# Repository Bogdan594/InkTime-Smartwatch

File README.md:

# InkTime - SmartWatch Project
InkTime este un concept de ceas inteligent axat pe eficienta energetica, utilizand un display e-Paper.

## Diagrama Bloc
```
┌─────────────────────────────────────────────────────────────┐
│                   SUBSISTEM ALIMENTARE                      │
│                                                             │
│  Port USB-C ─────► USBLC6-2SC6 (Protecție ESD)              │
│                          │                                  │
│                          ▼                                  │
│  Baterie Li-Po ◄────► BQ25180 (Încărcător IC)               │
│  (Test Pads)             │                                  │
│                          ▼                                  │
│                   RT6160AWSC (Buck-Boost) ──► VCC (3.3V)    │
│                          │                      (Sistem)    │
│                          ▼                                  │
│  MAX17048 (Fuel Gauge) ──► Monitorizare prin I2C            │
└─────────────────────────────────────────────────────────────┘

┌─────────────────────────────────────────────────────────────┐
│                  UNITATE DE PROCESARE                       │
│                                                             │
│              nRF52840 (MCU + Bluetooth LE)                  │
│        ┌─────────────┬─────────────┬─────────────┐          │
│        │             │             │             │          │
│     Bus SPI       Bus I2C       GPIOs        Antenă RF      │
│        │             │             │             │          │
│        ▼             │             ▼             ▼          │
│  Display e-Paper     │       3x Butoane      Johanson       │
│   (J1 - 24 pin)      │      (UP, DN, ENT)    2.45GHz        │
│                      │                                      │
│        ┌─────────────┴─────────────┐                        │
│        │                           │                        │
│        ▼                           ▼                        │
│  BMA423 (Accel.)          DRV2605L (Haptic)                 │
│  (Senzor mișcare)         (Motor Vibrații)                  │
└─────────────────────────────────────────────────────────────┘
```

## Bill of Materials

| Qty | Value | Device | Package | Parts | Description |
| :--- | :--- | :--- | :--- | :--- | :--- |
| 1 | - | ESP32_C6_LIBRARY_JUMPER | JUMPER_SJ | SJ1 | SMD solder JUMPER |
| 3 | 0 | CPF0201D7K68C1 | 0201 | R2, R3, R4 | 7.68k 0201 Thin Film Resistor |
| 4 | 0.1uF | GRM011R60J152KE01L | CAPC0201 | C23, C27, C34, C42 | SMD Capacitor X5R 6.3V |
| 1 | 0.1uF/50V | NRF_3_CAPACITOR_0201 | RESC0201 | EPD_C5 | Generic chip capacitor |
| 7 | 0.1uF/50V | NRF_3_CAPACITOR_0402 | RESC0402 | EPD_C6, EPD_C7, EPD_C8, EPD_C9, EPD_C10, EPD_C11, EPD_C12 | Generic chip capacitor |
| 1 | 0.47 | CPF0201D7K68C1 | 0201 | R1_EP_DR | 7.68k 0201 Resistor |
| 1 | 1.0uF | PERFECT_0402_CAP | 0402 | C15 | 0402 (1005 Metric) |
| 5 | 100nF | NRF_3_CAPACITOR_0201 | RESC0201 | C5, C7, C8, C12, C19 | Generic chip capacitor |
| 1 | 100pF | NRF_3_CAPACITOR_0201 | RESC0201 | C11 | Generic chip capacitor |
| 3 | 10K | CPF0201D7K68C1 | 0201 | R2_EP_DR, R9, R_PWR_EPD | 7.68k 0201 Resistor |
| 3 | 10k | CPF0201D7K68C1 | 0201 | R5, R7, R8 | 7.68k 0201 Resistor |
| 1 | 10uF | NRF_3_CAPACITOR_0402 | RESC0402 | C1-EP-DR | Generic chip capacitor |
| 2 | 10uF | PERFECT_0402_CAP | 0402 | C24, C39 | 0402 (1005 Metric) |
| 1 | 10uH | NRF_2_INDUCTOR_0402 | RESC0402 | L2 | Generic chip inductor |
| 4 | 12pF | NRF_3_CAPACITOR_0201 | RESC0201 | C1, C2, C17, C18 | Generic chip capacitor |
| 1 | 15nH | NRF_2_INDUCTOR_0402 | RESC0402 | L3 | Generic chip inductor |
| 2 | 1pF | NRF_3_CAPACITOR_0201 | RESC0201 | C3, C4 | Generic chip capacitor |
| 6 | 1uF | GRM011R60J152KE01L | CAPC0201 | C29, C30, C31, C32, C37, C38 | SMD Capacitor X5R 6.3V |
| 2 | 1uF/50V | NRF_3_CAPACITOR_0402 | RESC0402 | EPD_C1, EPD_C2 | Generic chip capacitor |
| 1 | 2.2 | CPF0201D7K68C1 | 0201 | R_TYPE_SEL | 7.68k 0201 Resistor |
| 3 | - | EVP-AKE31ASW | SW_EVP-AKE31A | SW_DN, SW_ENT, SW_UP | Panasonic Tactile Switch |
| 1 | 20V/4.2A | MOSFET_PCH-DMG2305UX | SOT23-3 | Q1 | P-channel MOSFET |
| 2 | 22uF | PERFECT_0402_CAP | 0402 | C25, C33 | 0402 (1005 Metric) |
| 1 | 2450AT18B100E | 2450AT18B100E | ANTC3216 | ANT1 | Antennas 2.45GHz ANTENNA |
| 1 | 3.9nH | NRF_2_INDUCTOR_0402 | RESC0402 | L1 | Generic chip inductor |
| 1 | 32.768kHz | NRF_1_XTAL_32KHZ | XTAL_3215 | X2 | Crystal Oscillator |
| 1 | 32MHz | NRF_XTAL_32MHZ | BT-XTAL_2016 | X1 | Crystal Oscillator |
| 2 | 3K3 | CPF0201D7K68C1 | 0201 | R17, R18 | 7.68k 0201 Resistor |
| 2 | 4.7uF | NRF_3_CAPACITOR_0402 | RESC0402 | C14, C43 | Generic chip capacitor |
| 1 | 4.7uF/25V | NRF_3_CAPACITOR_0402 | RESC0402 | C2-EP-DR | Generic chip capacitor |
| 3 | 4.7µF | PERFECT_0402_CAP | 0402 | C6, C20, C21 | 0402 (1005 Metric) |
| 1 | 47nF | PERFECT_0402_CAP | 0402 | C16 | 0402 (1005 Metric) |
| 1 | 503480-2400 | 503480-2400 | 5034802400 | J1 | 0.5mm FPC RA SMT 24Ckt |
| 2 | 5K1 | CPF0201D7K68C1 | 0201 | R1_USB, R2_USB | 7.68k 0201 Resistor |
| 1 | 68uH | 744043680IND | IND_4828 | L5 | Wurth Electronics Inductor |
| 1 | 820pF | NRF_3_CAPACITOR_0201 | RESC0201 | C9 | Generic chip capacitor |
| 1 | BMA421 | BMA423 | BMA423 | IC3 | Accelerometer Triaxial |
| 1 | BQ25180YBGR | BQ25180YBGR | BGA8 | IC1 | Charger IC Li-Ion/Polymer |
| 1 | DRV2605YZFR | DRV2605YZFR | BGA9 | IC2 | Haptic Driver |
| 1 | FTC252012S | MLP2016SR47 | INDC2016 | L7 | SMD / SMT Inductor 0.47uH |
| 14 | - | HECTOR_WATCH_TP | TP20R | TP_3.3V ... TP_VREG | Test pads |
| 1 | KH-TYPE-C-16P | KH-TYPE-C-16P | SMT | J4 | USB Type-C Connector |
| 1 | MAX17048G+T | MAX17048G | SON50P200 | U3 | Fuel Gauge with ModelGauge |
| 3 | MBR0530 | MBR0530 | SOD3716 | D2, D4, D5 | Schottky Diode 0.5A 30V |
| 3 | N.C. | NRF_3_CAPACITOR_0201 | RESC0201 | C10, C13, C22 | Not Connected |
| 1 | NRF52840_QF | NRF52840_QF | AQFN-74 | U1 | nRF52840 SoC |
| 1 | RT6160AWSC | RT6160AWSC | BGA15 | IC9 | Buck-Boost Regulator |
| 1 | SI1308EDL | SI1308EDL | SOT65P210

## Functionalitati Hardware

- Unitate Centrala: nRF52840 gestioneaza logica sistemului si conexiunea Bluetooth 5.4 prin arhitectura ARM Cortex-M4F.
- Afisaj: Ecranul e-Paper de 1.54" utilizeaza interfata SPI pentru a mentine imaginea afisata cu consum zero de energie.
- Senzori Miscare: Accelerometrul BMA423 comunica prin I2C pentru a detecta pasii si gesturile de activare a ecranului.
- Feedback Haptic: Driverul DRV2605L utilizeaza magistrala I2C pentru a genera efecte de vibratie precise prin motorul intern.
- Gestiune Energie: Integratul BQ25180 controleaza incarcarea bateriei prin USB-C, asigurand protectia si longevitatea celulei Li-Po.
- Stabilizare Tensiune: Regulatorul Buck-Boost RT6160A mentine un prag constant de 3.3V necesar functionarii stabile a componentelor.
- Monitorizare Baterie: Cipul MAX17048 raporteaza prin I2C nivelul de incarcare (SOC%) folosind algoritmi de masurare fara rezistor de sunt.
- Eficienta: Combinatia dintre MCU-ul ultra-low-power si display-ul e-Paper permite o autonomie estimata de peste 60 de zile.

## Configuratia pinilor nRF52840

- Bus SPI (P0.11-P0.15): Folosit pentru Display-ul e-Paper deoarece asigura latimea de banda mare necesara pentru transferul rapid al bufferului de imagine.
- Bus I2C (P0.26, P0.27): Conecteaza senzorii (BMA423, MAX17048) si driverele (DRV2605, BQ25180) pe aceleasi doua fire pentru a minimiza numarul de trasee pe PCB.
- Pini Butoane (P0.02, P0.03, P0.28): Alocati ca intrari digitale cu intreruperi (GPIOTE) pentru a permite trezirea instanta a ceasului din modul de consum redus (Deep Sleep).
- Pin Busy Display (P0.16): Intrare digitala care permite MCU-ului sa astepte pana cand ecranul termina procesul fizic de refresh inainte de a trimite noi date.
- Pin Interrupt BMA423 (P0.19): Conectat la MCU pentru a semnaliza detectia miscarii (wrist-tilt) fara ca procesorul sa interogheze constant senzorul, economisind energie.
- Pin Enable Haptic (P0.20): Pin de control rapid pentru driverul DRV2605L, utilizat pentru a declansa secventele de vibratii sincronizate cu notificarile.
- Pini Cristal 32MHz (XC1, XC2): Pini dedicati pentru oscilatorul extern de mare precizie, critic pentru functionarea corecta a radioului Bluetooth Low Energy.
- Pini Cristal 32.768kHz (P0.00, P0.01): Folositi pentru ceasul de timp real (RTC) care asigura masurarea precisa a orei cu un consum de curent de ordinul microamperilor.
- Pini SWD (SWDIO, SWDCLK): Interfata dedicata de programare si debug, absolut necesara pentru incarcarea firmware-ului si monitorizarea variabilelor in timp real.
- Pin Reset (P0.18): Configurat ca intrare de reset hardware pentru a permite repornirea sigura a sistemului in cazul unui blocaj software (Watchdog/Manual).

## Decizii luate
- Am acceptat erorile de overlap pe pinii procesorului cauzate de via-uri deoarece nu am gasit o alta metoda de a trage cablu pana acolo.
- Am acceptat erorile de copper clearence pentru ca orice alta solutie ar fi ingreunat si mai tare asezarea cablurilor.
- Am acceptat erorile de airwire intrucat gasirea unui traseu intre 2 acei pini ar fi provocat mai multe erori de alte tipuri

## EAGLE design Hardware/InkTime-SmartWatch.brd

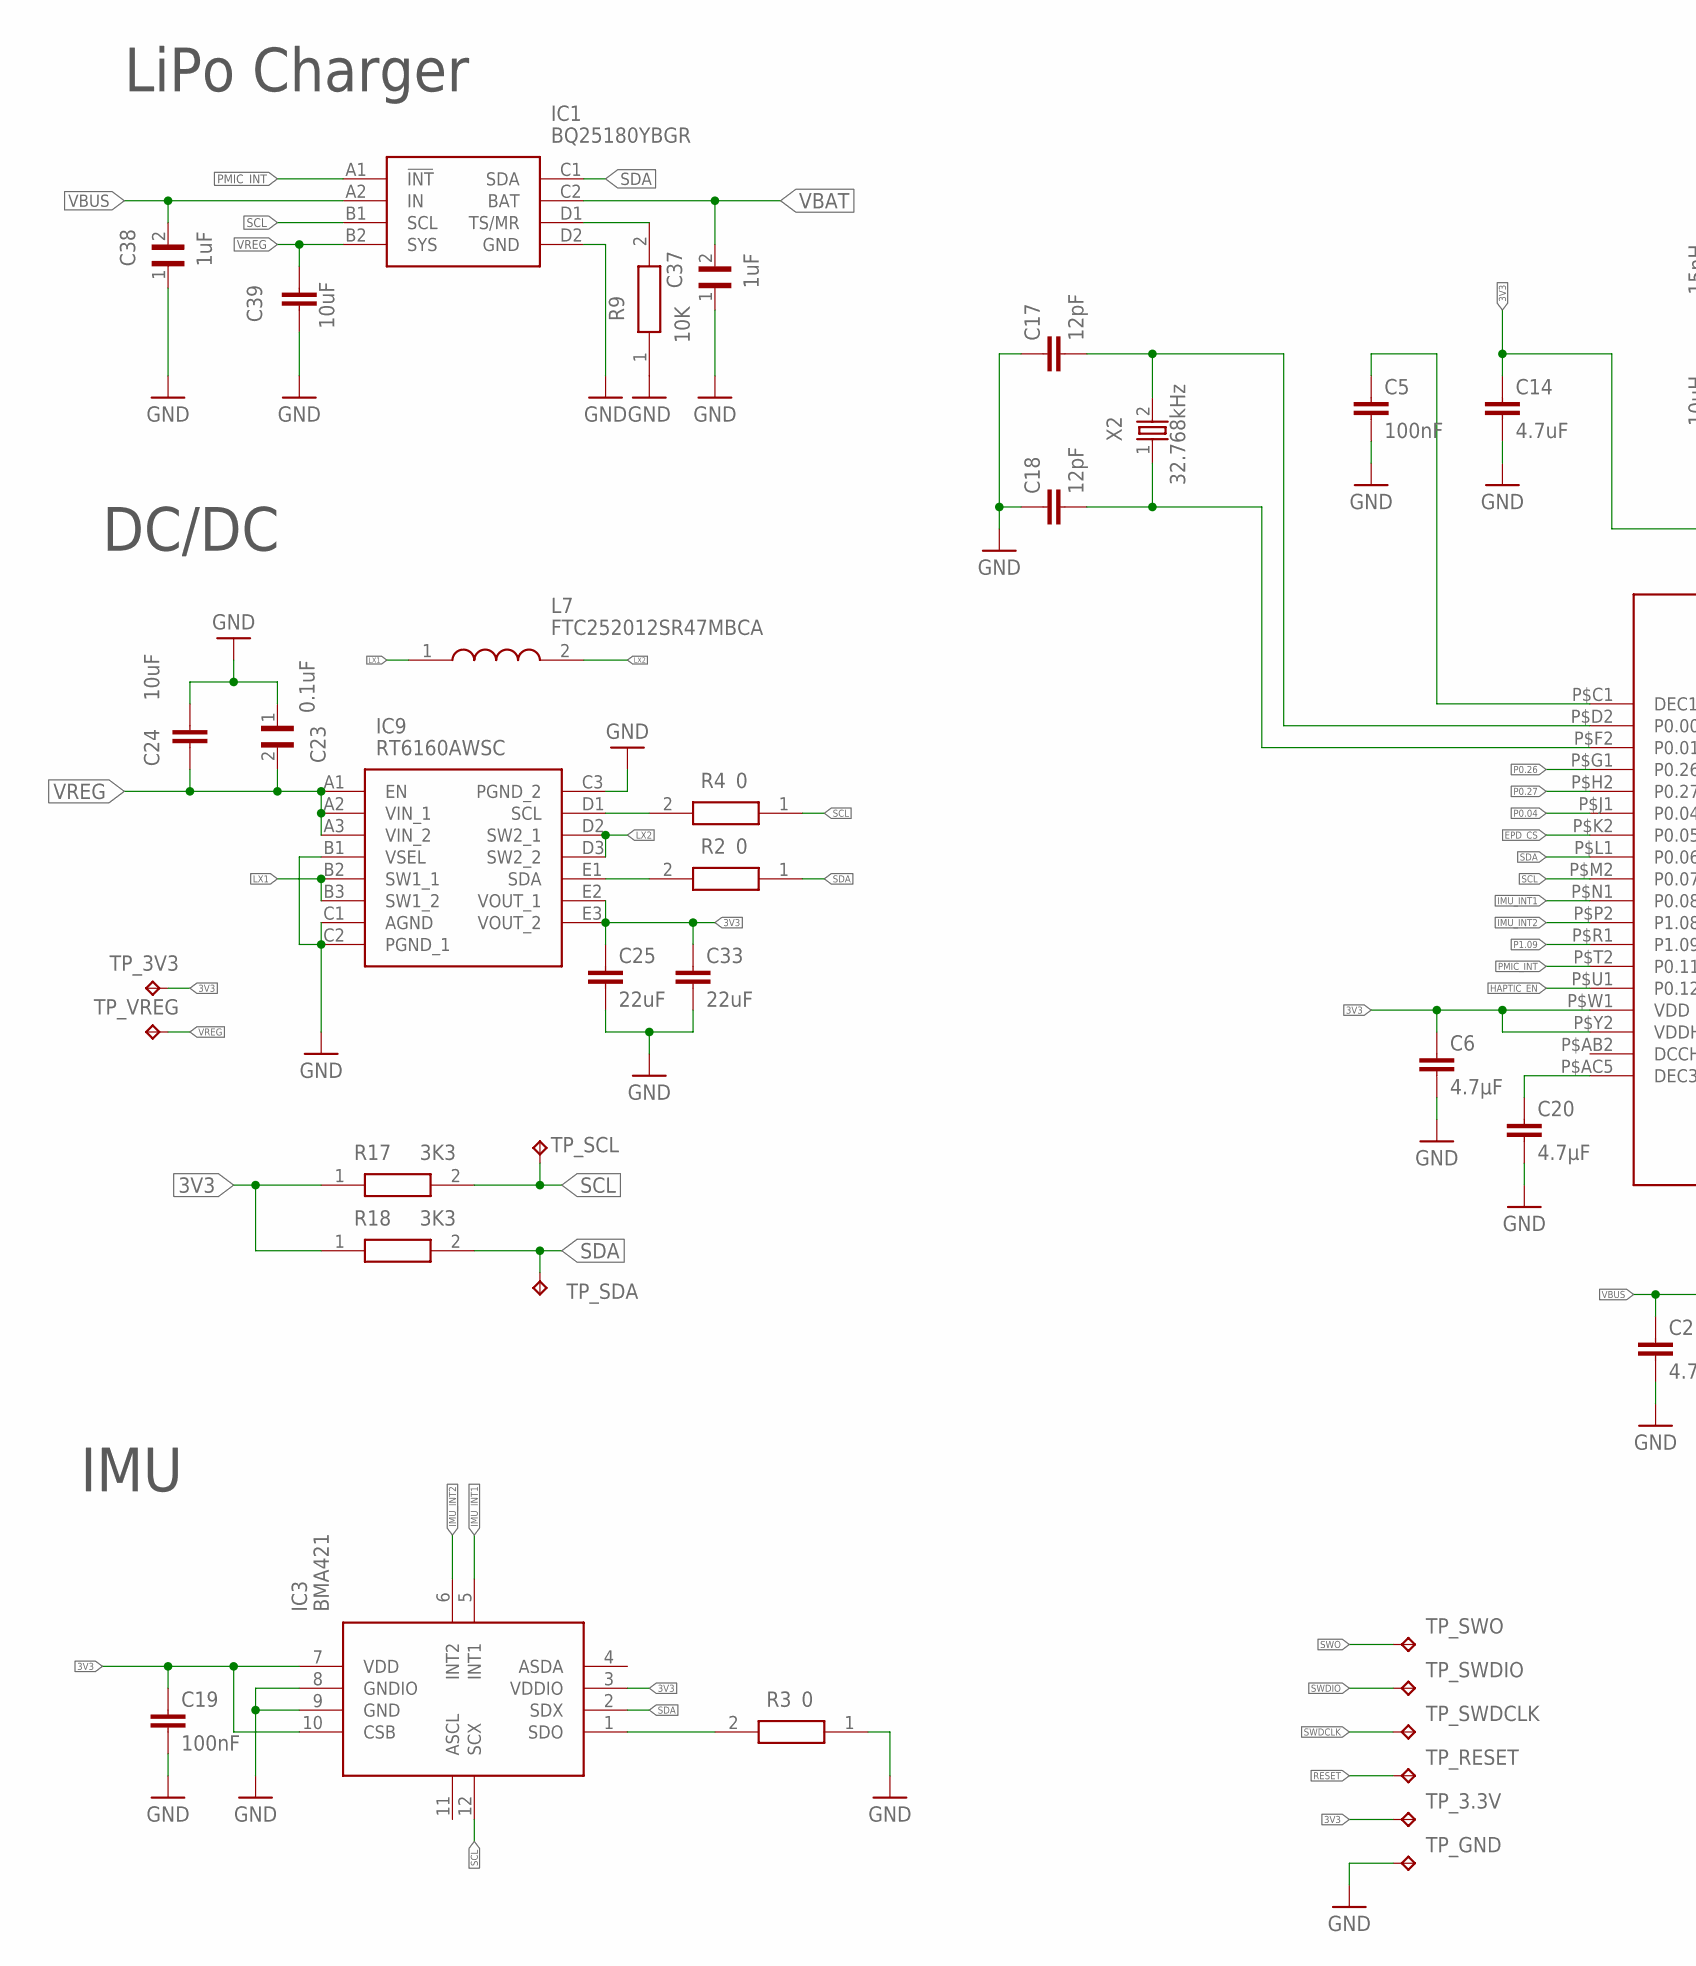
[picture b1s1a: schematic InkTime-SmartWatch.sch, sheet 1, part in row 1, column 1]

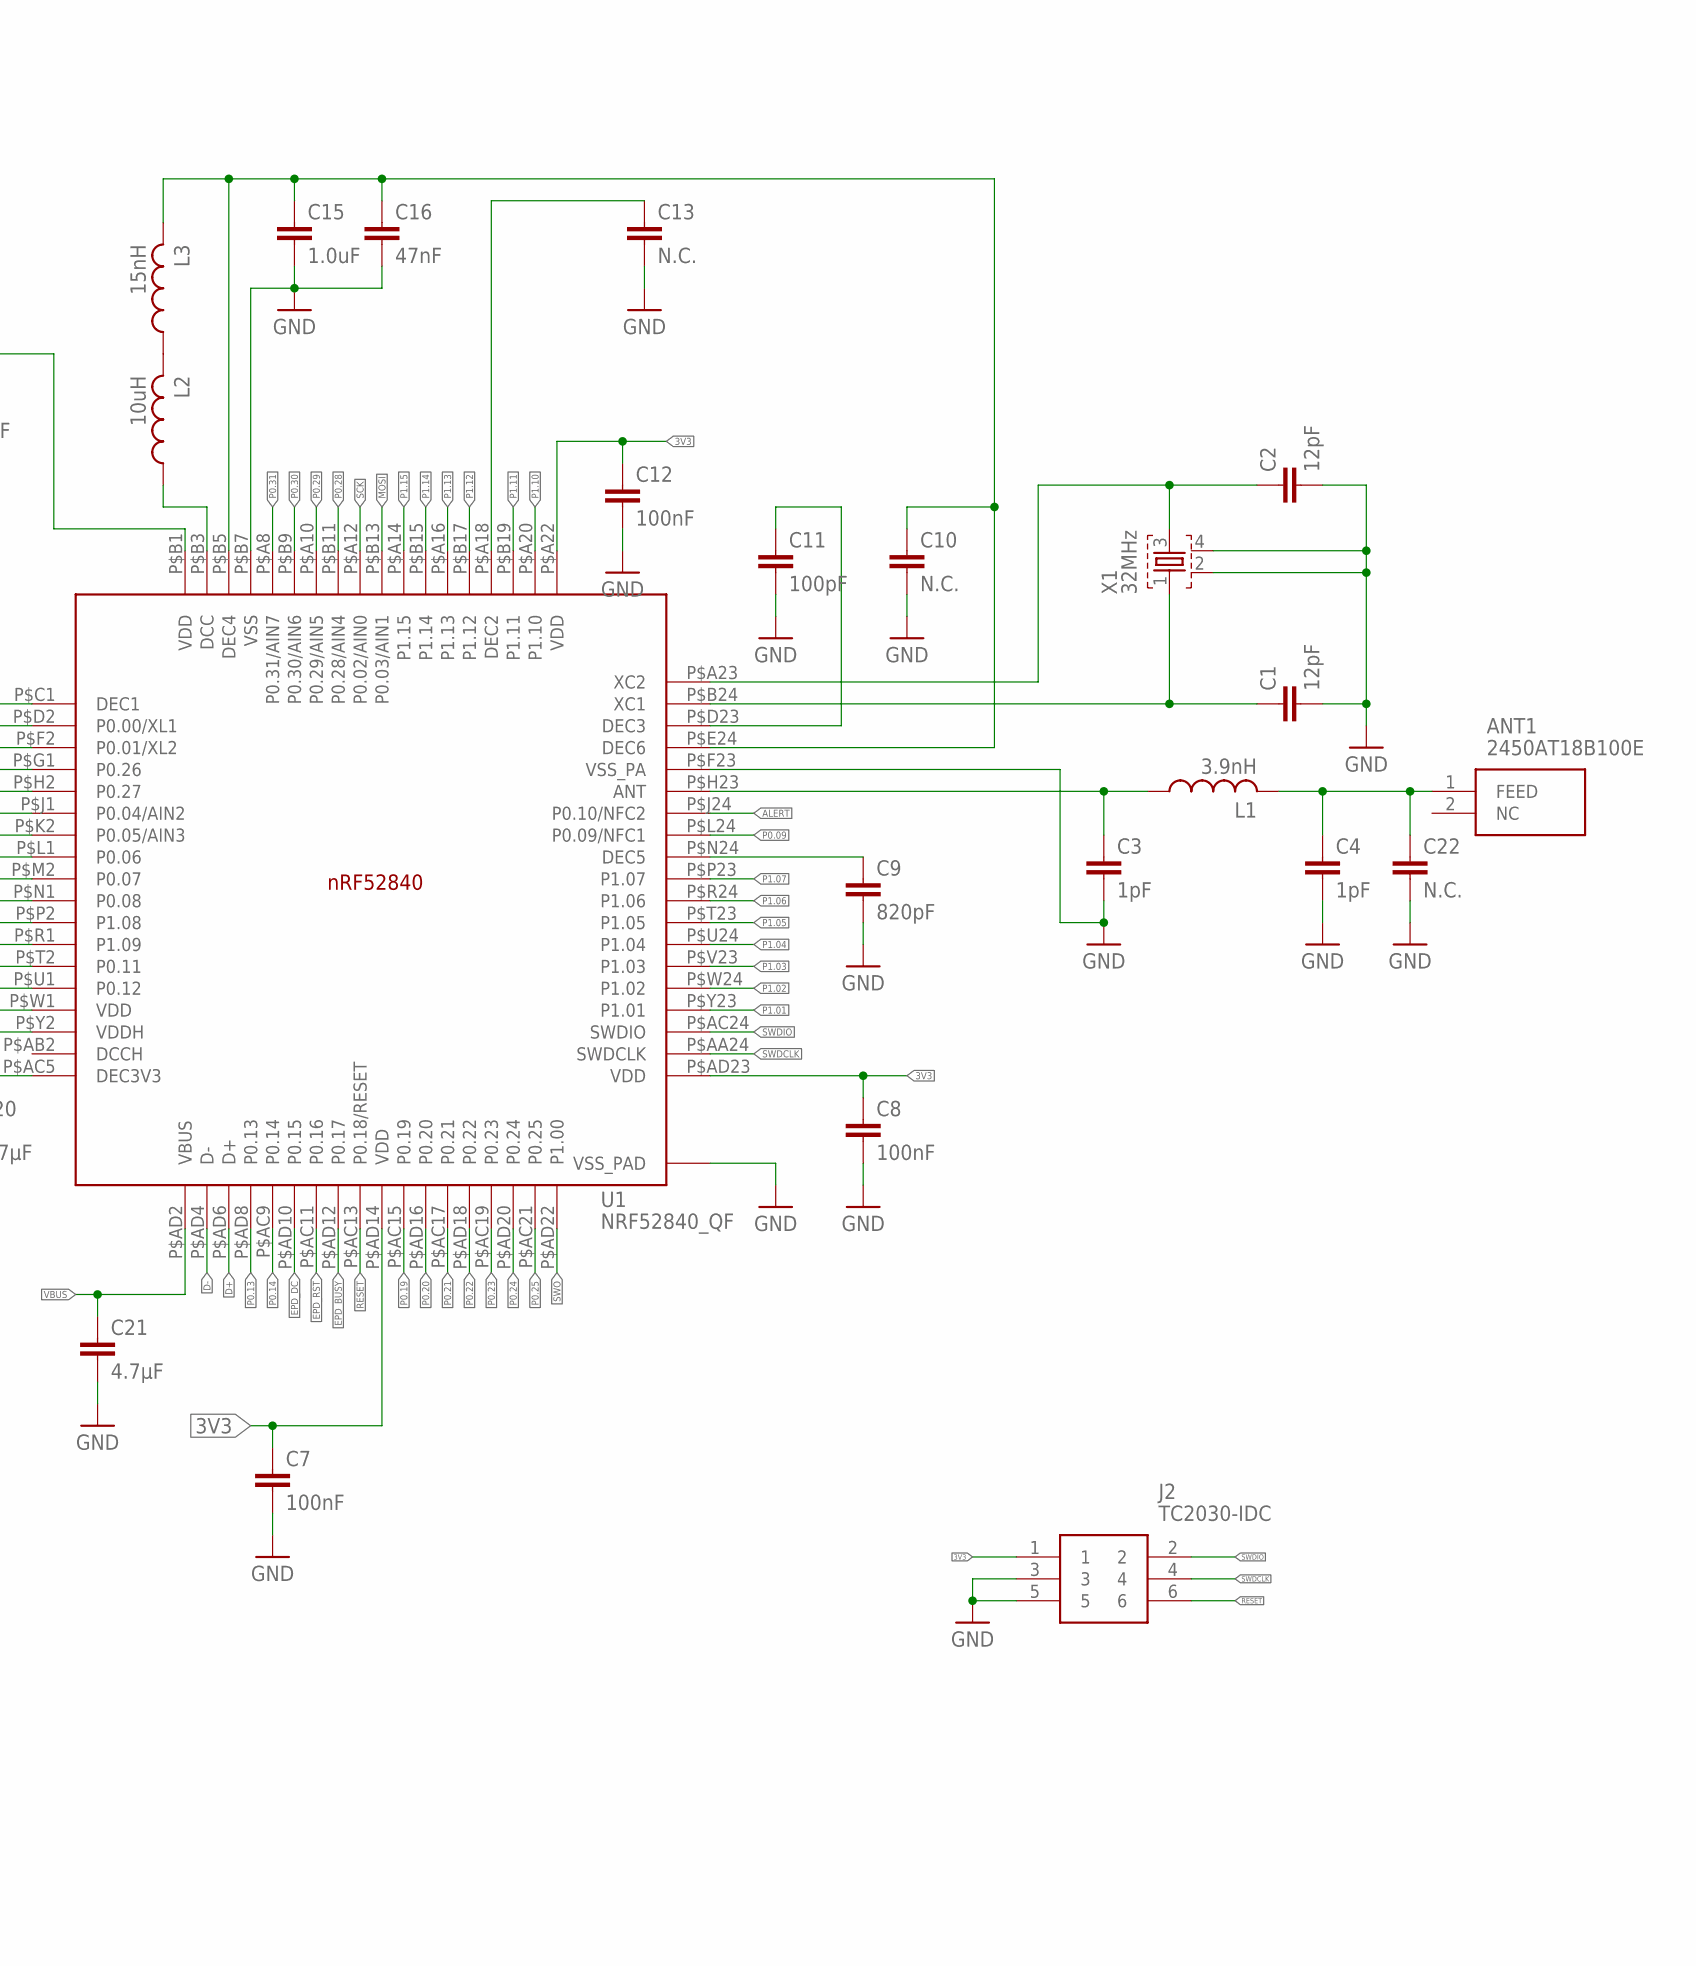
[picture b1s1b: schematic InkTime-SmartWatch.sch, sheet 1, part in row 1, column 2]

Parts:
ANT1: 2450AT18B100E; 2450AT18B100E_ANTC3216X140N
C1, C2, C17, C18: 12pF; NORDIC_NRF_3_RESC0201_L
C3, C4: 1pF; NORDIC_NRF_3_RESC0201_L
C5, C7, C8, C12, C19: 100nF; NORDIC_NRF_3_RESC0201_L
C6, C20, C21: 4.7μF; PERFECT_0402_0402
C9: 820pF; NORDIC_NRF_3_RESC0201_L
C10, C13, C22: N.C.; NORDIC_NRF_3_RESC0201_L
C11: 100pF; NORDIC_NRF_3_RESC0201_L
C14: 4.7uF; NORDIC_NRF_3_RESC0402_L
C15: 1.0uF; PERFECT_0402_0402
C16: 47nF; PERFECT_0402_0402
C23: 0.1uF; GRM011R60J152KE01L_2_CAPC0201X13N
C24, C39: 10uF; PERFECT_0402_0402
C25, C33: 22uF; PERFECT_0402_0402
C37, C38: 1uF; GRM011R60J152KE01L_2_CAPC0201X13N
IC1: BQ25180YBGR; BQ25180YBGR_BGA8C40P2X4_100X155X50
IC3: BMA421; BMA423_BMA423
IC9: RT6160AWSC; RT6160AWSC_BGA15C40P3X5_140X230X60
J2: TC2030-IDC; TC2030-IDC_TC2030IDC
L1: 3.9nH; NORDIC_NRF_2_RESC0402_L
L2: 10uH; NORDIC_NRF_2_RESC0402_L
L3: 15nH; NORDIC_NRF_2_RESC0402_L
L7: FTC252012SR47MBCA; MLP2016SR47MT0S1_INDC2016X100N
R2, R3, R4: 0; CPF0201D7K68C1_0201
R9: 10K; CPF0201D7K68C1_0201
R17, R18: 3K3; CPF0201D7K68C1_0201
TP_3.3V, TP_3V3: HECTOR_WATCH_1_TPTP20R; HECTOR_WATCH_1_TP20R
TP_GND: HECTOR_WATCH_1_TPTP20R; HECTOR_WATCH_1_TP20R
TP_RESET: HECTOR_WATCH_1_TPTP20R; HECTOR_WATCH_1_TP20R
TP_SCL: HECTOR_WATCH_1_TPTP20R; HECTOR_WATCH_1_TP20R
TP_SDA: HECTOR_WATCH_1_TPTP20R; HECTOR_WATCH_1_TP20R
TP_SWDCLK: HECTOR_WATCH_1_TPTP20R; HECTOR_WATCH_1_TP20R
TP_SWDIO: HECTOR_WATCH_1_TPTP20R; HECTOR_WATCH_1_TP20R
TP_SWO: HECTOR_WATCH_1_TPTP20R; HECTOR_WATCH_1_TP20R
TP_VREG: HECTOR_WATCH_1_TPTP20R; HECTOR_WATCH_1_TP20R
U1: NRF52840_QF; NORDIC_NRF_4_AQFN50P700X700X85_HS-74N
X1: 32MHz; NORDIC_NRF_BT-XTAL_2016_N
X2: 32.768kHz; NORDIC_NRF_1_XTAL_3215_N

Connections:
3V3: C6.1, C7.1, C8.1, C12.1, C14.1, C19.1, C25.1, C33.1, IC3.3 (VDDIO), IC3.7 (VDD), IC3.10 (CSB), IC9.E2 (VOUT_1), IC9.E3 (VOUT_2), J2.1, R17.1, R18.1, TP_3.3V.TP, TP_3V3.TP, U1.P$A22 (VDD), U1.P$AD14 (VDD), U1.P$AD23 (VDD), U1.P$B1 (VDD), U1.P$W1 (VDD), U1.P$Y2 (VDDH); also elsewhere on the board
ALERT: U1.P$J24 (P0.10/NFC2); also elsewhere on the board
D+: U1.P$AD6 (D+); also elsewhere on the board
D-: U1.P$AD4 (D-); also elsewhere on the board
EPD_BUSY: U1.P$AD12 (P0.17); also elsewhere on the board
EPD_CS: U1.P$K2 (P0.05/AIN3); also elsewhere on the board
EPD_DC: U1.P$AD10 (P0.15); also elsewhere on the board
EPD_RST: U1.P$AC11 (P0.16); also elsewhere on the board
GND: C1.2, C2.2, C3.2, C4.2, C5.2, C6.2, C7.2, C8.2, C9.2, C10.2, C11.2, C12.2, C13.2, C14.2, C15.2, C16.2, C17.1, C18.1, C19.2, C20.2, C21.2, C22.2, C23.1, C24.1, C25.2, C33.2, C37.1, C38.1, C39.2, IC1.D2 (GND), IC3.8 (GNDIO), IC3.9 (GND), IC9.B1 (VSEL), IC9.C1 (AGND), IC9.C2 (PGND_1), IC9.C3 (PGND_2), J2.3, J2.5, R3.1, R9.1, TP_GND.TP, U1.P$74 (VSS_PAD), U1.P$75 (VSS_PAD), U1.P$76 (VSS_PAD), U1.P$77 (VSS_PAD), U1.P$78 (VSS_PAD), U1.P$79 (VSS_PAD), U1.P$80 (VSS_PAD), U1.P$81 (VSS_PAD), U1.P$82 (VSS_PAD), U1.P$83 (VSS_PAD), U1.P$84 (VSS_PAD), U1.P$85 (VSS_PAD), U1.P$86 (VSS_PAD), U1.P$87 (VSS_PAD), U1.P$88 (VSS_PAD), U1.P$89 (VSS_PAD), U1.P$90 (VSS_PAD), U1.P$B7 (VSS), U1.P$F23 (VSS_PA), X1.2, X1.4; also elsewhere on the board
HAPTIC_EN: U1.P$U1 (P0.12); also elsewhere on the board
IMU_INT1: IC3.5 (INT1), U1.P$N1 (P0.08)
IMU_INT2: IC3.6 (INT2), U1.P$P2 (P1.08)
LX1: IC9.B2 (SW1_1), IC9.B3 (SW1_2), L7.1
LX2: IC9.D2 (SW2_1), IC9.D3 (SW2_2), L7.2
MOSI: U1.P$B13 (P0.03/AIN1); also elsewhere on the board
unnamed: C2.1, U1.P$A23 (XC2), X1.3
unnamed: C3.1, L1.1, U1.P$H23 (ANT)
unnamed: C1.1, U1.P$B24 (XC1), X1.1
unnamed: C11.1, U1.P$D23 (DEC3)
unnamed: C9.1, U1.P$N24 (DEC5)
unnamed: ANT1.1 (FEED), C4.1, C22.1, L1.2
unnamed: C20.1, U1.P$AC5 (DEC3V3)
unnamed: C5.1, U1.P$C1 (DEC1)
unnamed: C17.2, U1.P$D2 (P0.00/XL1), X2.2
unnamed: C18.2, U1.P$F2 (P0.01/XL2), X2.1
unnamed: C13.1, U1.P$A18 (DEC2)
unnamed: IC9.E1 (SDA), R2.2
unnamed: IC3.1 (SDO), R3.2
unnamed: IC9.D1 (SCL), R4.2
unnamed: C10.1, C15.1, C16.1, L3.2, U1.P$B5 (DEC4), U1.P$E24 (DEC6)
unnamed: IC1.D1 (TS/MR), R9.2
unnamed: L2.1, U1.P$B3 (DCC)
unnamed: L2.2, L3.1
P0.04: U1.P$J1 (P0.04/AIN2)
P0.09: U1.P$L24 (P0.09/NFC1)
P0.13: U1.P$AD8 (P0.13); also elsewhere on the board
P0.14: U1.P$AC9 (P0.14); also elsewhere on the board
P0.19: U1.P$AC15 (P0.19)
P0.20: U1.P$AD16 (P0.20)
P0.21: U1.P$AC17 (P0.21)
P0.22: U1.P$AD18 (P0.22)
P0.23: U1.P$AC19 (P0.23)
P0.24: U1.P$AD20 (P0.24)
P0.25: U1.P$AC21 (P0.25)
P0.26: U1.P$G1 (P0.26)
P0.27: U1.P$H2 (P0.27)
P0.28: U1.P$B11 (P0.28/AIN4)
P0.29: U1.P$A10 (P0.29/AIN5)
P0.30: U1.P$B9 (P0.30/AIN6)
P0.31: U1.P$A8 (P0.31/AIN7)
P1.01: U1.P$Y23 (P1.01); also elsewhere on the board
P1.02: U1.P$W24 (P1.02); also elsewhere on the board
P1.03: U1.P$V23 (P1.03)
P1.04: U1.P$U24 (P1.04)
P1.05: U1.P$T23 (P1.05)
P1.06: U1.P$R24 (P1.06)
P1.07: U1.P$P23 (P1.07)
P1.09: U1.P$R1 (P1.09)
P1.10: U1.P$A20 (P1.10)
P1.11: U1.P$B19 (P1.11)
P1.12: U1.P$B17 (P1.12)
P1.13: U1.P$A16 (P1.13)
P1.14: U1.P$B15 (P1.14)
P1.15: U1.P$A14 (P1.15)
PMIC_INT: IC1.A1 (!INT), U1.P$T2 (P0.11)
RESET: J2.6, TP_RESET.TP, U1.P$AC13 (P0.18/RESET)
SCK: U1.P$A12 (P0.02/AIN0); also elsewhere on the board
SCL: IC1.B1 (SCL), IC3.12 (SCX), R4.1, R17.2, TP_SCL.TP, U1.P$M2 (P0.07); also elsewhere on the board
SDA: IC1.C1 (SDA), IC3.2 (SDX), R2.1, R18.2, TP_SDA.TP, U1.P$L1 (P0.06); also elsewhere on the board
SWDCLK: J2.4, TP_SWDCLK.TP, U1.P$AA24 (SWDCLK)
SWDIO: J2.2, TP_SWDIO.TP, U1.P$AC24 (SWDIO)
SWO: TP_SWO.TP, U1.P$AD22 (P1.00)
VBAT: C37.2, IC1.C2 (BAT); also elsewhere on the board
VBUS: C21.1, C38.2, IC1.A2 (IN), U1.P$AD2 (VBUS); also elsewhere on the board
VREG: C23.2, C24.2, C39.1, IC1.B2 (SYS), IC9.A1 (EN), IC9.A2 (VIN_1), IC9.A3 (VIN_2), TP_VREG.TP

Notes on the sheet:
LiPo Charger
DC/DC
IMU

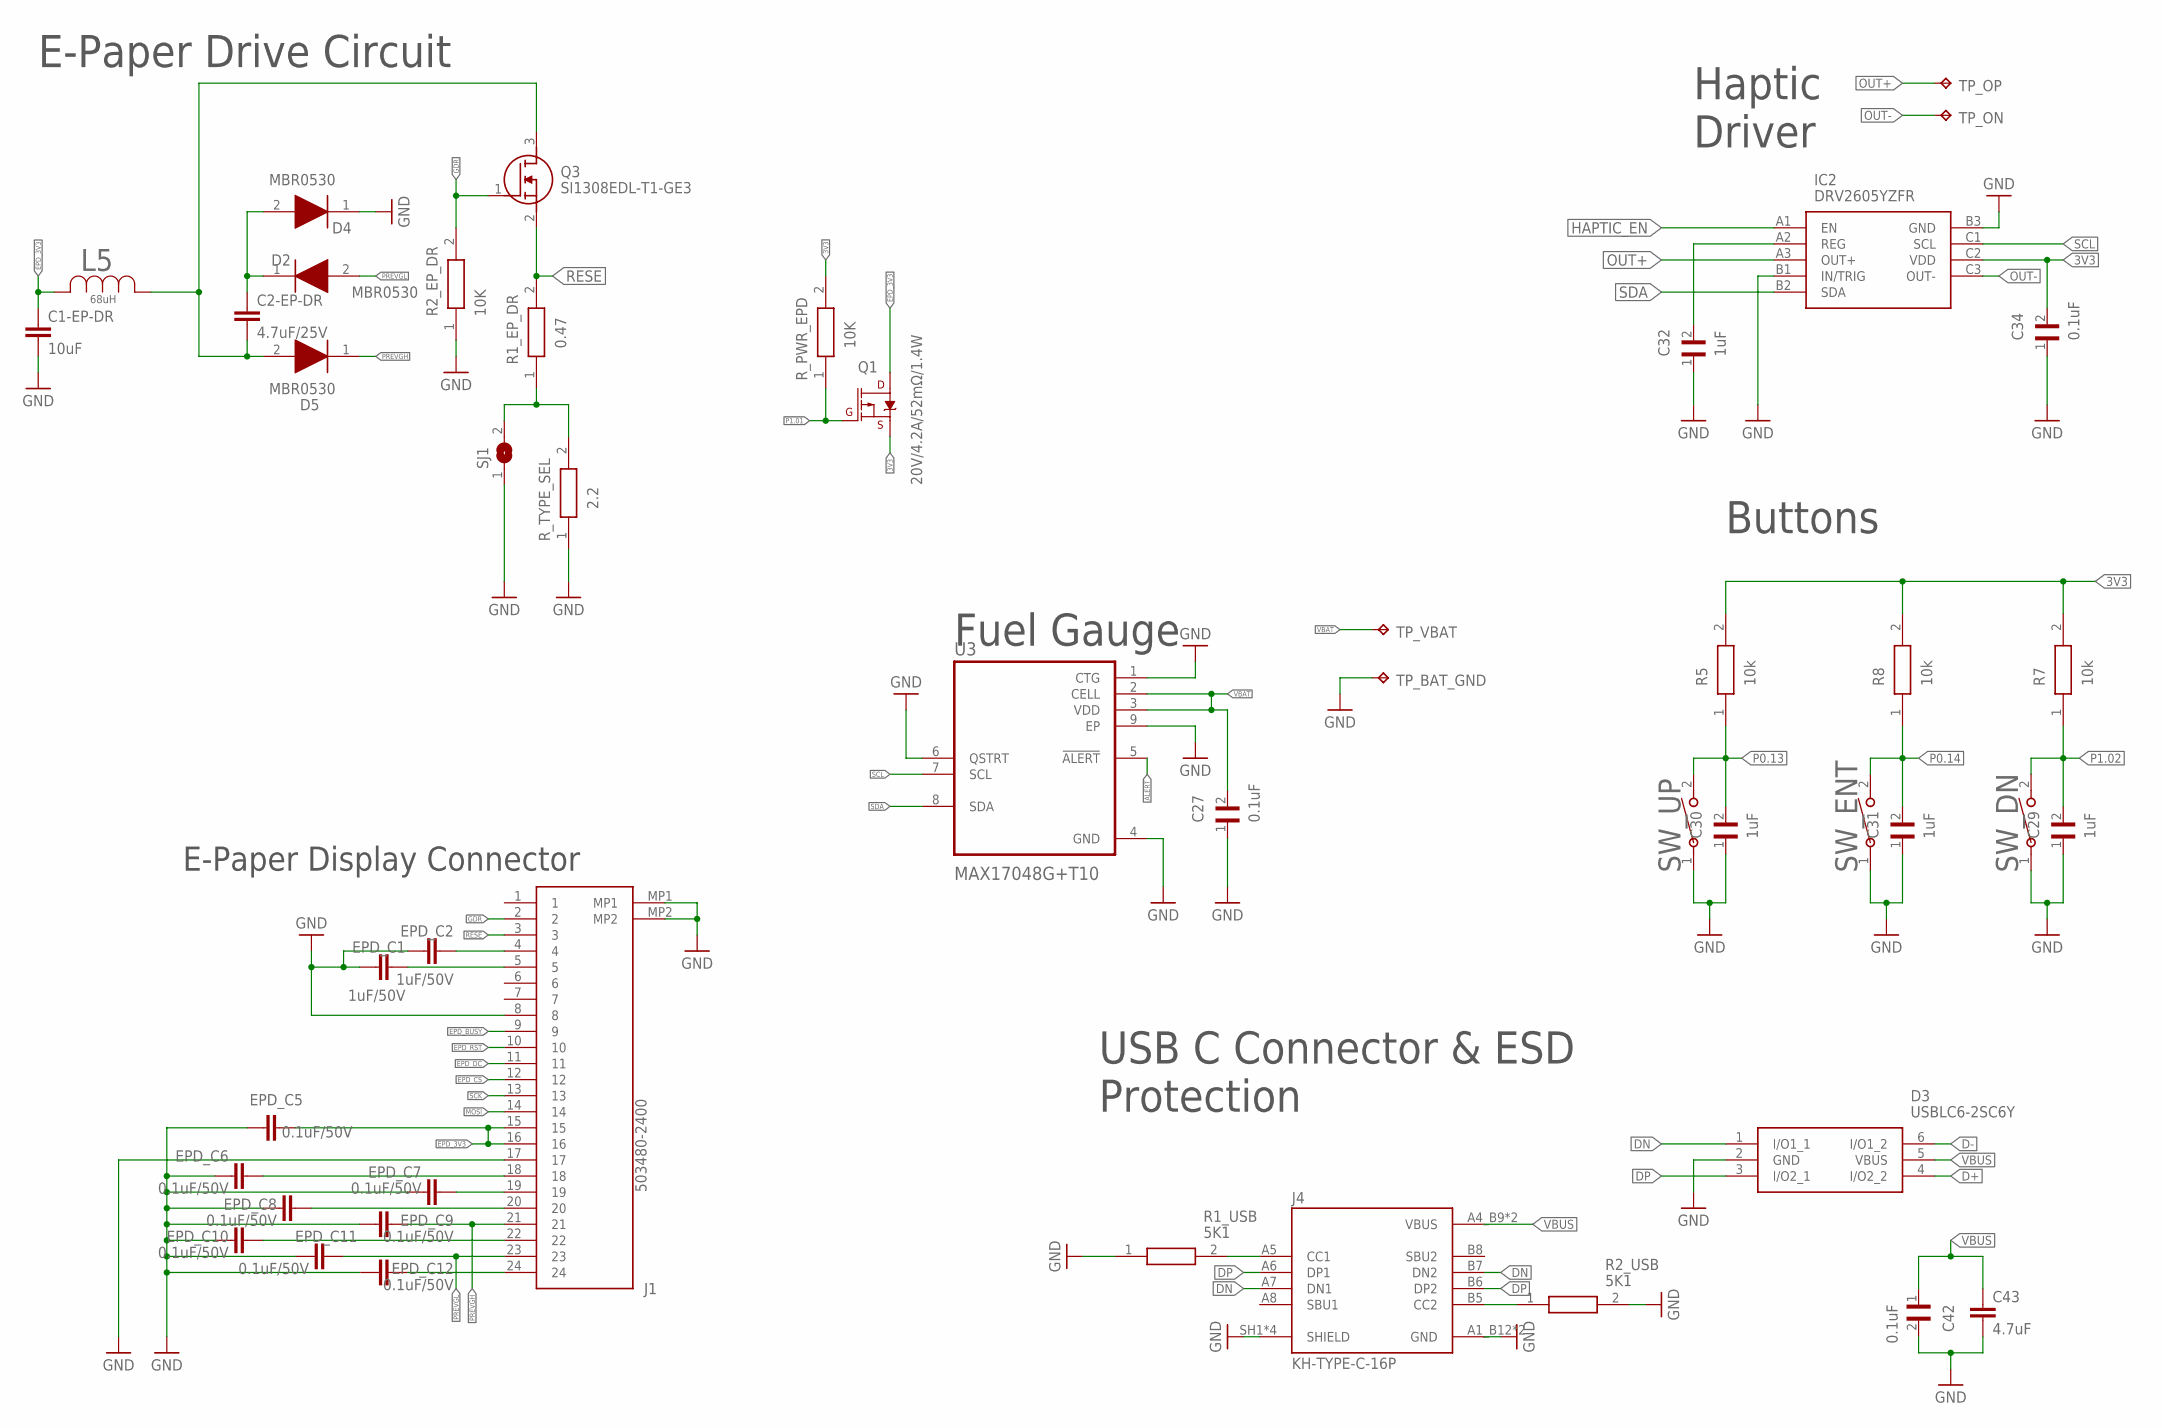
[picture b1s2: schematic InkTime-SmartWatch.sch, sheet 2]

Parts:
C1-EP-DR: 10uF; NORDIC_NRF_3_RESC0402_L
C2-EP-DR: 4.7uF/25V; NORDIC_NRF_3_RESC0402_L
C27, C34, C42: 0.1uF; GRM011R60J152KE01L_2_CAPC0201X13N
C29, C30, C31, C32: 1uF; GRM011R60J152KE01L_2_CAPC0201X13N
C43: 4.7uF; NORDIC_NRF_3_RESC0402_L
D2, D4, D5: MBR0530; ESP32_C6_LIBRARY_5_SOD3716X135N
D3: USBLC6-2SC6Y; ESP32_C6_LIBRARY_3_SOT95P280X145-6N
EPD_C1, EPD_C2: 1uF/50V; NORDIC_NRF_3_RESC0402_L
EPD_C5: 0.1uF/50V; NORDIC_NRF_3_RESC0201_L
EPD_C6, EPD_C7, EPD_C8, EPD_C9, EPD_C10, EPD_C11, EPD_C12: 0.1uF/50V; NORDIC_NRF_3_RESC0402_L
IC2: DRV2605YZFR; DRV2605YZFR_BGA9C50P3X3_144X144X62
J1: 503480-2400; 503480-2400_5034802400
J4: KH-TYPE-C-16P; KH-TYPE-C-16P_KINGHELM_KH-TYPE-C-16P
L5: 68uH; ESP32_C6_LIBRARY_2_IND_4828-WE-TPC_WRE
Q1: 20V/4.2A/52mΩ/1.4W; ESP32_C6_LIBRARY_4_ESP32_C6_LIBRARY_4_ESP32_C6_LIBRARY_4_ES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
Q3: SI1308EDL-T1-GE3; ESP32_C6_LIBRARY_6_SOT65P210X110-3N
R1_EP_DR: 0.47; CPF0201D7K68C1_0201
R1_USB, R2_USB: 5K1; CPF0201D7K68C1_0201
R2_EP_DR: 10K; CPF0201D7K68C1_0201
R5, R7, R8: 10k; CPF0201D7K68C1_0201
R_PWR_EPD: 10K; CPF0201D7K68C1_0201
R_TYPE_SEL: 2.2; CPF0201D7K68C1_0201
SJ1: ESP32_C6_LIBRARY_7_JUMPER_SJ
SW_DN: 2025-10-22_07-23-44_LIBRARY_EVP-AKE31ASW_EVP-AKE3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; 2025-10-22_07-23-44_LIBRARY_SW_EVP-AKE31A_PAN
SW_ENT: 2025-10-22_07-23-44_LIBRARY_EVP-AKE31ASW_EVP-AKE3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; 2025-10-22_07-23-44_LIBRARY_SW_EVP-AKE31A_PAN
SW_UP: 2025-10-22_07-23-44_LIBRARY_EVP-AKE31ASW_EVP-AKE3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; 2025-10-22_07-23-44_LIBRARY_SW_EVP-AKE31A_PAN
TP_BAT_GND: HECTOR_WATCH_1_TPTP20R; HECTOR_WATCH_1_TP20R
TP_ON: HECTOR_WATCH_1_TPTP20R; HECTOR_WATCH_1_TP20R
TP_OP: HECTOR_WATCH_1_TPTP20R; HECTOR_WATCH_1_TP20R
TP_VBAT: HECTOR_WATCH_1_TPTP20R; HECTOR_WATCH_1_TP20R
U3: MAX17048G+T10; ESP32_C6_LIBRARY_SON50P200X200X80-9N

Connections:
3V3: C34.2, IC2.C2 (VDD), Q1.2 (S), R5.2, R7.2, R8.2, R_PWR_EPD.2; also elsewhere on the board
ALERT: U3.5 (!ALERT); also elsewhere on the board
D+: D3.4 (I/O2_2); also elsewhere on the board
D-: D3.6 (I/O1_2); also elsewhere on the board
DN: D3.1 (I/O1_1), J4.A7 (DN1), J4.B7 (DN2)
DP: D3.3 (I/O2_1), J4.A6 (DP1), J4.B6 (DP2)
EPD_3V3: C1-EP-DR.1, EPD_C5.1, J1.15, J1.16, L5.2, Q1.3 (D)
EPD_BUSY: J1.9; also elsewhere on the board
EPD_CS: J1.12; also elsewhere on the board
EPD_DC: J1.11; also elsewhere on the board
EPD_RST: J1.10; also elsewhere on the board
GDR: J1.2, Q3.1 (G), R2_EP_DR.2
GND: C1-EP-DR.2, C27.1, C29.1, C30.1, C31.1, C32.1, C34.1, C42.2, C43.2, D3.2 (GND), D4.1 (K), EPD_C1.1, EPD_C2.1, EPD_C5.2, EPD_C6.1, EPD_C7.1, EPD_C8.1, EPD_C9.1, EPD_C10.1, EPD_C11.1, EPD_C12.1, IC2.B1 (IN/TRIG), IC2.B3 (GND), J1.8, J1.17, J1.MP1, J1.MP2, J4.A1_B12 (GND), J4.A12_B1 (GND), J4.SH1 (SHIELD), J4.SH2 (SHIELD), J4.SH3 (SHIELD), J4.SH4 (SHIELD), R1_USB.1, R2_EP_DR.1, R2_USB.2, R_TYPE_SEL.1, SJ1.1, SW_DN.1, SW_ENT.1, SW_UP.1, TP_BAT_GND.TP, U3.1 (CTG), U3.4 (GND), U3.6 (QSTRT), U3.9 (EP); also elsewhere on the board
HAPTIC_EN: IC2.A1 (EN); also elsewhere on the board
MOSI: J1.14; also elsewhere on the board
unnamed: EPD_C6.2, J1.18
unnamed: EPD_C7.2, J1.19
unnamed: EPD_C2.2, J1.4
unnamed: EPD_C1.2, J1.5
unnamed: EPD_C8.2, J1.20
unnamed: C2-EP-DR.2, D5.2 (A), L5.1, Q3.3 (D)
unnamed: EPD_C10.2, J1.22
unnamed: C2-EP-DR.1, D2.1 (K), D4.2 (A)
unnamed: EPD_C12.2, J1.24
unnamed: R1_EP_DR.1, R_TYPE_SEL.2, SJ1.2
unnamed: C32.2, IC2.A2 (REG)
unnamed: J4.B5 (CC2), R2_USB.1
unnamed: J4.A5 (CC1), R1_USB.2
OUT+: IC2.A3 (OUT+), TP_OP.TP
OUT-: IC2.C3 (OUT-), TP_ON.TP
P0.13: C30.2, R5.1, SW_UP.2; also elsewhere on the board
P0.14: C31.2, R8.1, SW_ENT.2; also elsewhere on the board
P1.01: Q1.1 (G), R_PWR_EPD.1; also elsewhere on the board
P1.02: C29.2, R7.1, SW_DN.2; also elsewhere on the board
PREVGH: D5.1 (K), EPD_C9.2, J1.21
PREVGL: D2.2 (A), EPD_C11.2, J1.23
RESE: J1.3, Q3.2 (S), R1_EP_DR.2
SCK: J1.13; also elsewhere on the board
SCL: IC2.C1 (SCL), U3.7 (SCL); also elsewhere on the board
SDA: IC2.B2 (SDA), U3.8 (SDA); also elsewhere on the board
VBAT: C27.2, TP_VBAT.TP, U3.2 (CELL), U3.3 (VDD); also elsewhere on the board
VBUS: C42.1, C43.1, D3.5 (VBUS), J4.A4_B9 (VBUS), J4.A9_B4 (VBUS); also elsewhere on the board

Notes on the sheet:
USB C Connector & ESD
Protection
Buttons
Fuel Gauge
E-Paper Drive Circuit
Haptic Driver
E-Paper Display Connector

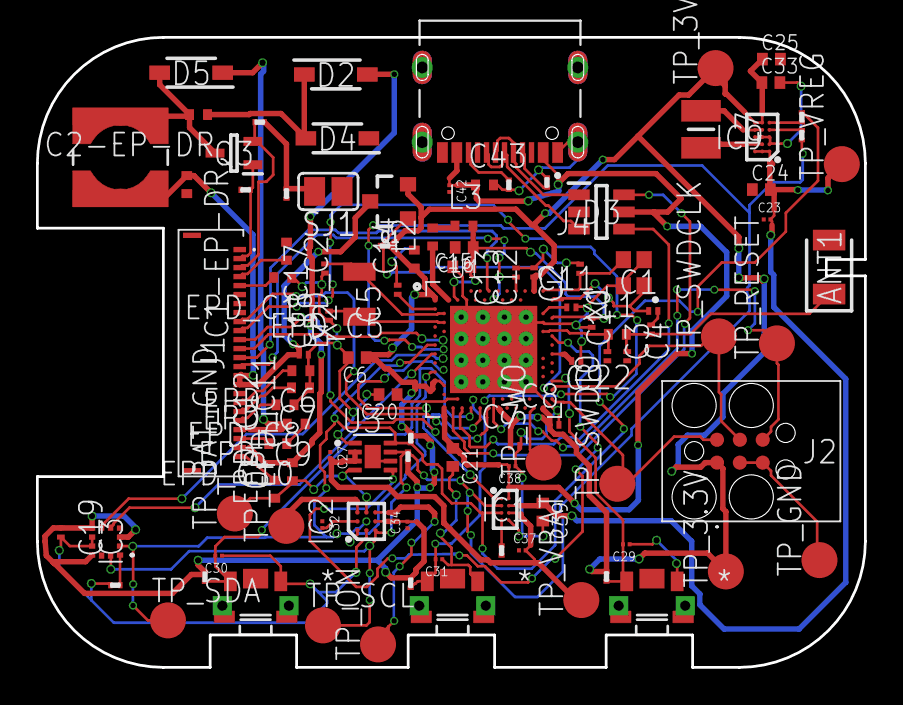
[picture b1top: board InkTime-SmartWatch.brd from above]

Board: 2 copper layers, 46.0 x 35.0 mm, 105 parts (0 on the bottom side), 70 nets.

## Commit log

2026-04-18 Varianta finala de PCB 2D
2026-04-20 Modele 3D
2026-04-20 Mai multe poze
2026-04-20 Add project title to README.md
2026-04-20 Fix spelling and enhance hardware functionalities section
    Corrected spelling mistakes and added hardware functionality details.
2026-04-20 Varianta finala

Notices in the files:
parts and their libraries:
COPYRIGHT: Copyright (C) 2024 Ultra Librarian. All rights reserved.
COPYRIGHT: Copyright (C) 2025 Ultra Librarian. All rights reserved.
